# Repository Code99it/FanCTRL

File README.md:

# FanCTRL

Controls the fan speed using an additional PCB, especially for fans with a 4-pin connector (plus, minus, PWM, tacho).

## Features

* **4-Pin Fan Support:** Full control over standard 4-pin cooling fans, utilizing all signals:
  * **Power:** `V+` (Plus)
  * **Ground:** `GND` (Minus)
  * **PWM:** Precise speed control via Pulse Width Modulation.
  * **Tacho:** RPM feedback interpretation (Tachometer signal).
* **Dedicated Hardware:** Designed to offload fan management to a custom, additional PCB.
* **Efficient Control:** Optimized timing and frequency handling for silent and reliable fan operation.

## Pinout & Signals

| Pin | Description | Signal Type |
| :--- | :--- | :--- |
| **+** / **V+** | Power Supply | Input (e.g., 12V) |
| **-** / **GND**| Ground | Reference |
| **PWM** | Pulse Width Modulation | Control Input (Target Speed) |
| **TACHO** | Tachometer / FG | Output (RPM Feedback) |

## Hardware Setup

Connect the 4-pin fan connector directly to the designated header on the FanCTRL PCB. Ensure that the logic level of the microcontroller (e.g., 3.3V or 5V) matches the PWM input specifications of your fan or is properly shifted on the PCB.

## Getting Started

1. Clone the repository:
   ```bash
   git clone https://github.com/Code99it/FanCTRL.git

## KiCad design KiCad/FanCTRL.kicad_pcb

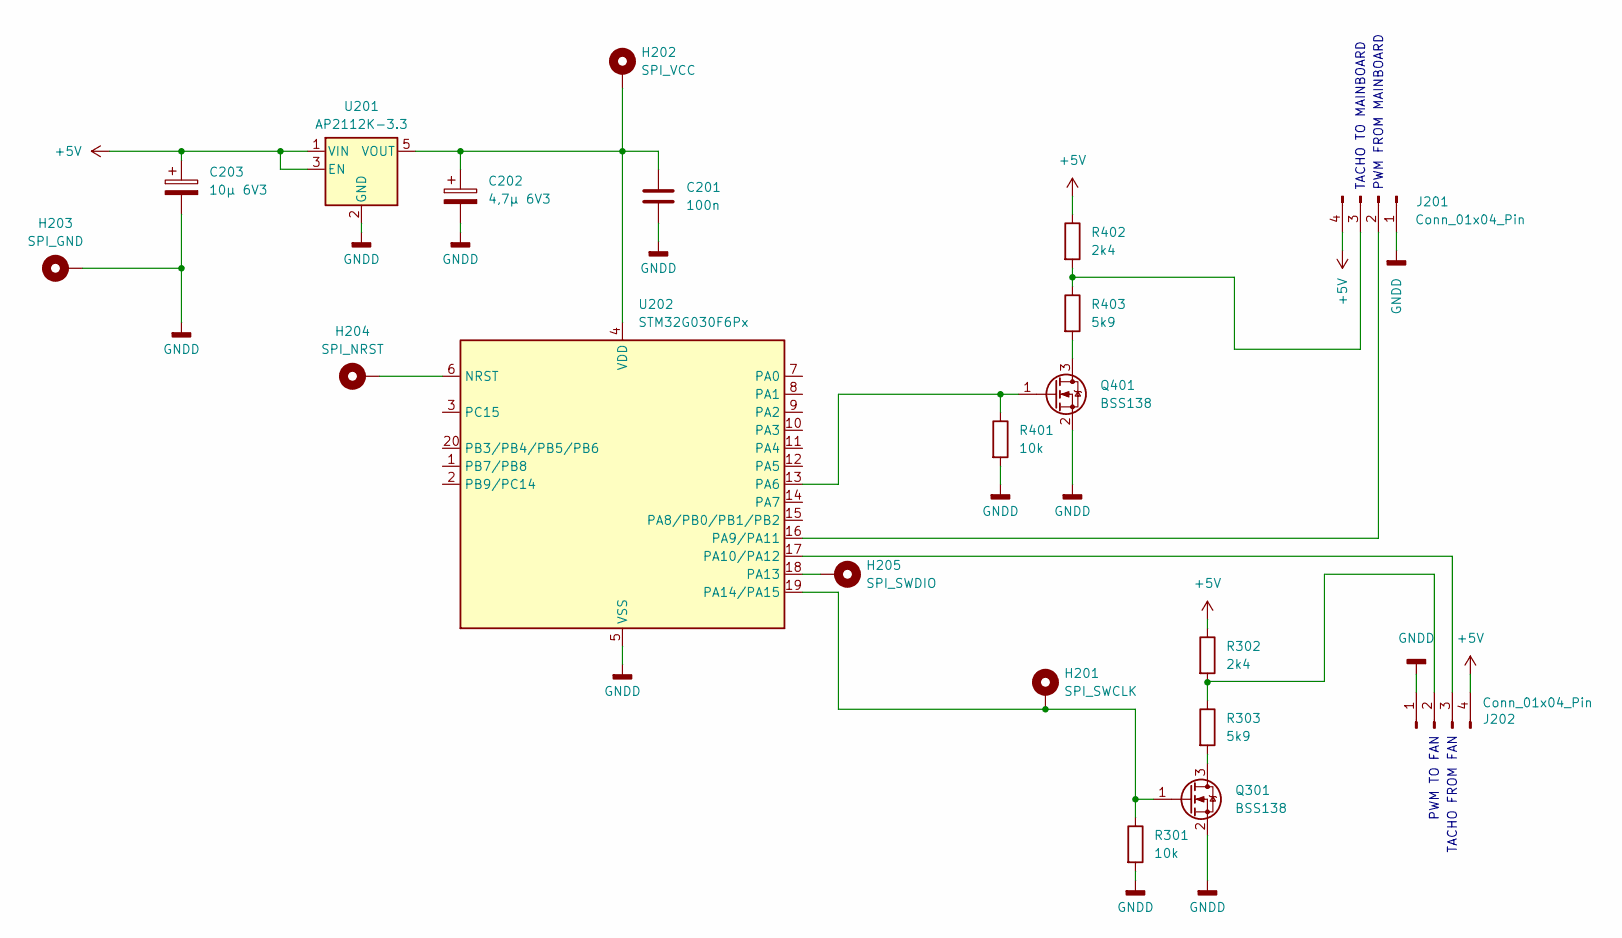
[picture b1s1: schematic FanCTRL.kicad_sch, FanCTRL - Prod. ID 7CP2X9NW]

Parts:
C201: 100n; C_0805_2012Metric
C202: 4,7µ 6V3; CP_Elec_4x3.9
C203: 10µ 6V3; CP_Elec_5x4.5
H201: SPI_SWCLK; TestPoint_Pad_1.5x1.5mm
H202: SPI_VCC; TestPoint_Pad_1.5x1.5mm
H203: SPI_GND; TestPoint_Pad_1.5x1.5mm
H204: SPI_NRST; TestPoint_Pad_1.5x1.5mm
H205: SPI_SWDIO; TestPoint_Pad_1.5x1.5mm
J201, J202: Conn_01x04_Pin; JST_SH_SM04B-SRSS-TB_1x04-1MP_P1.00mm_Horizontal
Q301, Q401: BSS138; SOT-23
R301, R401: 10k; R_0805_2012Metric
R302, R402: 2k4; R_0805_2012Metric
R303, R403: 5k9; R_0805_2012Metric
U201: AP2112K-3.3; SOT-23-5
U202: STM32G030F6Px; TSSOP-20_4.4x6.5mm_P0.65mm

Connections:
+5V: C203.1, J201.4, J202.4, R302.1, R402.1, U201.1 (VIN), U201.3 (EN)
GNDD: C201.2, C202.2, C203.2, H203.1, J201.1, J202.1, Q301.2 (S), Q401.2 (S), R301.2, R401.2, U201.2 (GND), U202.5 (VSS)
unnamed: J201.2, U202.16 (PA9/PA11)
unnamed: J201.3, R402.2, R403.1
unnamed: J202.2, R302.2, R303.1
unnamed: J202.3, U202.17 (PA10/PA12)
unnamed: Q301.3 (D), R303.2
unnamed: H201.1, Q301.1 (G), R301.1, U202.19 (PA14/PA15)
unnamed: Q401.3 (D), R403.2
unnamed: Q401.1 (G), R401.1, U202.13 (PA6)
unnamed: C201.1, C202.1, H202.1, U201.5 (VOUT), U202.4 (VDD)
unnamed: H204.1, U202.6 (NRST)
unnamed: H205.1, U202.18 (PA13)

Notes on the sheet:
TACHO TO MAINBOARD
PWM TO FAN
PWM FROM MAINBOARD
TACHO FROM FAN

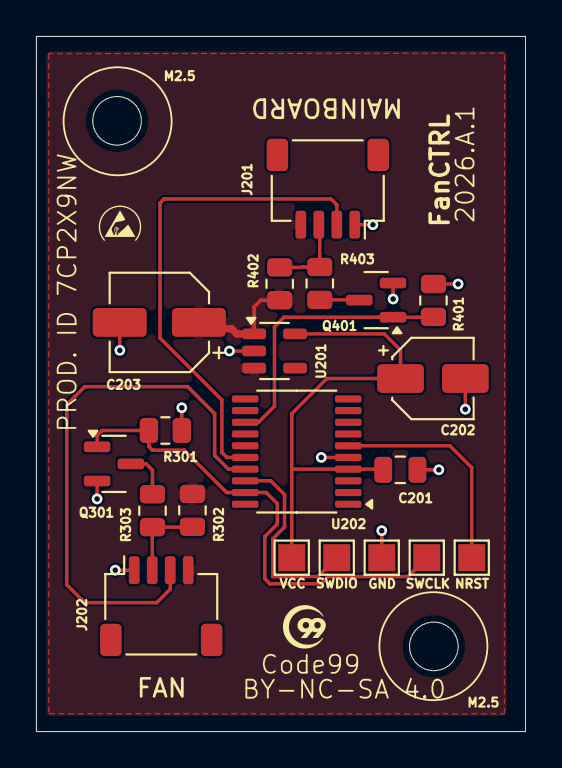
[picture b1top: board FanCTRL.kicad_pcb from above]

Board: 2 copper layers, 27.2 x 38.6 mm, 20 parts (0 on the bottom side), 13 nets.

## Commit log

2026-05-25 Initial Commit, containing all KiCad files
2026-05-25 Added README
2026-05-25 Edited README
2026-05-25 Added and edited some Texts in Schematic and Board

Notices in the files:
KiCad/FanCTRL.kicad_pcb:
Copyright: Christian Wilhelm (cw1@code99.it)
License: Creative Commons BY-NC-SA 4.0
